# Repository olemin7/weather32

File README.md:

weather stantion
redused CPU frequency to 80
# Troubleshooting

* Program upload failure

    * Hardware connection is not correct: run `idf.py -p PORT monitor`, and reboot your board to see if there are any output logs.
    * The baud rate for downloading is too high: lower your baud rate in the `menuconfig` menu, and try again.

https://esp-idf-lib.readthedocs.io/en/latest/groups/bmp180.html

https://github.com/espressif/esp-iot-solution

# esp32c3_supermini
    Pin     | ADC | func |
GPIO_NUM_0  | A0  |      |photoresistor
GPIO_NUM_1  | A1  |      |service switch
GPIO_NUM_2  | A2  |      |
GPIO_NUM_3  | A3  |      |
GPIO_NUM_4  | A4  | SCK  | 
3V3
GND
5V
-------------------------------------
GPIO_NUM_5  | A5  | MISO |
GPIO_NUM_6  |     | MOSI | bme680 SDA !!! swap in new PCB version
GPIO_NUM_7  |     | SS   | bme680 SDL
GPIO_NUM_8  |     | SDA  | LED           
GPIO_NUM_9  |     | SDL  | BOOT_BUTTON   
GPIO_NUM_10 |     |      |
GPIO_NUM_20 |     | RX   |
GPIO_NUM_21 |     | TX   |

https://github.com/DiegoPaezA/ESP32-freeRTOS/blob/master/i2c_scanner/main/i2c_scanner.c
https://github.com/espressif/esp-iot-solution/tree/dd15770d0f8c5fedea78809737f04b63d3765c83/examples/sensors/sensor_hub_monitor

. /home/oleksandr/ides/tools/esp-idf-v5.3/export.sh
export IOT_SOLUTION_PATH=/home/oleksandr/personal/repo/esp-iot-solution
idf.py set-target esp32c3
idf.py build
idf.py menuconfig

null in the env https://github.com/espressif/idf-eclipse-plugin/issues/535https://components.espressif.com/

Check the values in your sdkconfig for LOG_MAXIMUM_LEVEL. It defaults to matching LOG_DEFAULT_LEVEL which limits what values you can use by default.

# mqtt test
sudo apt-get install mosquitto mosquitto-clients

sudo vim /etc/mosquitto/mosquitto.conf 
add
  listener 1883 0.0.0.0
  allow_anonymous true

sudo ufw allow 1883

sudo /etc/init.d/mosquitto restart

mosquitto_sub -h nas.local -d -t advertisement
mosquitto_pub -h nas.local -d -t cmd -m "adv"
mosquitto_sub -h 192.168.1.2 -d -t devices/64E833880880/#

one terminal
mosquitto_sub -d -t hello/world
mosquitto_sub -d -t stat/weather -h central.local
Connect to another ssh session and run
mosquitto_pub -d -t hello/world -m "Hello from terminal window 2!"

sudo tail -f /var/log/mosquitto/mosquitto.log

mosquitto_sub -h nas.local -d -t '#'
https://github.com/nopnop2002/esp-idf-json/tree/master/json-basic-object

# button
todo boot btn to go provision mode?

# esp-idf-lib
https://esp-idf-lib.readthedocs.io/en/latest/index.html
git clone git@github.com:UncleRus/esp-idf-lib.git

# dependency
https://github.com/olemin7/esp32_idf_libs

# TP4056  li ion charger
max 4.2
min 2.5
## li ion
max 4.2
min 3.0

## attenuation
ADC_ATTEN_DB_0   100 mV ~ 950 mV
ADC_ATTEN_DB_2_5 100 mV ~ 1250 mV
ADC_ATTEN_DB_6   150 mV ~ 1750 mV
ADC_ATTEN_DB_12  150 mV ~ 2450 mV

https://docs.espressif.com/projects/esp-idf/en/v4.4.8/esp32/api-reference/peripherals/adc.html
#photoresistor (GND ) -photoresistor- (A0) -resistor 10k- (+3.3)

# LiIon
min 
https://esp32tutorials.com/esp32-esp-idf-max7219-dot-matrix-display

[json]
https://github.com/nopnop2002/esp-idf-json

# cmd list
export TARGET_MAC=64E833885558
export TARGET_MAC=64E833880880
export TARGET_MAC=64E83387D7D0
export TARGET_MAC=64E8338811DC
mosquitto_sub -d -t response/$TARGET_MAC -h nas.local
mosquitto_sub -d -t devices/$TARGET_MAC/# -h nas.local

mosquitto_pub -d -t cmd/$TARGET_MAC -m '{"cmd":"help"}' -h nas.local

mosquitto_pub -d -t cmd/$TARGET_MAC -m '{"cmd":"ldr","payload":{"min":100,"max":3000}}' -h nas.local
mosquitto_pub -d -t cmd/$TARGET_MAC -m '{"cmd":"restart"}' -h nas.local

mosquitto_pub -d -t cmd/$TARGET_MAC -m '{"cmd":"brightness","payload":{"points":[{"lighting":1530,"brightness":10}]}}' -h nas.local

mosquitto_pub -d -t cmd/$TARGET_MAC -m -h nas.local '{"cmd":"brightness","payload":{"points":[{"lighting":1530,"brightness":10}]}}' 

{"cmd":"display","payload":{"segment_rotation":0,"segment_upsidedown":false,"mirrored":false}}

'{"cmd":"display","payload":{"segment_rotation":3,"segment_upsidedown":true,"mirrored":true}}

'{"cmd":"timezone","payload":{"tz":"GMT-3"}}'

[http command server]
url /cmd
smd the same as for mosqitoo
[IDF_PATH]

printenv IDF_PATH

export IDF_PATH="/home/oleksandrminenko/personal/esp-idf/v5.4/esp-idf"

[TODO]
custom data when provision

[test]
https://www.throwtheswitch.org/unity
idf.py -p /dev/ttyACM0 flash

[mink]
long press on boot btn ->reprovision

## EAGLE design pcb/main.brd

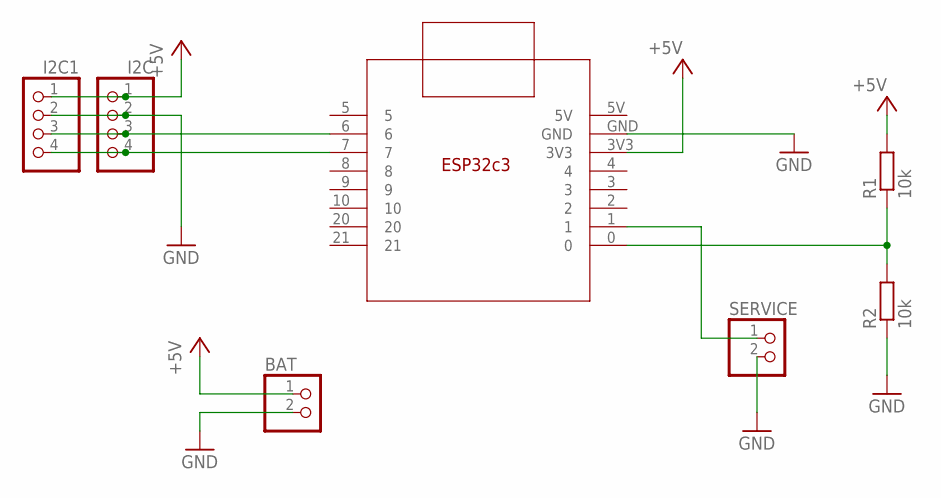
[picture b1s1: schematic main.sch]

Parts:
BAT: PINHD-1X2; 1X02
I2C, I2C1: PINHD-1X4; 1X04
R1, R2: 10k; R0805
SERVICE: PINHD-1X2; 1X02
U$2: ESP32C3SMD; ESP32C3_SMD

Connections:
+5V: BAT.1, I2C.1, I2C1.1, R1.2, U$2.3V3
GND: BAT.2, I2C.2, I2C1.2, R2.1, SERVICE.2, U$2.GND
unnamed: I2C.3, I2C1.3, U$2.6
unnamed: R1.1, R2.2, U$2.0
unnamed: I2C.4, I2C1.4, U$2.7
unnamed: SERVICE.1, U$2.1

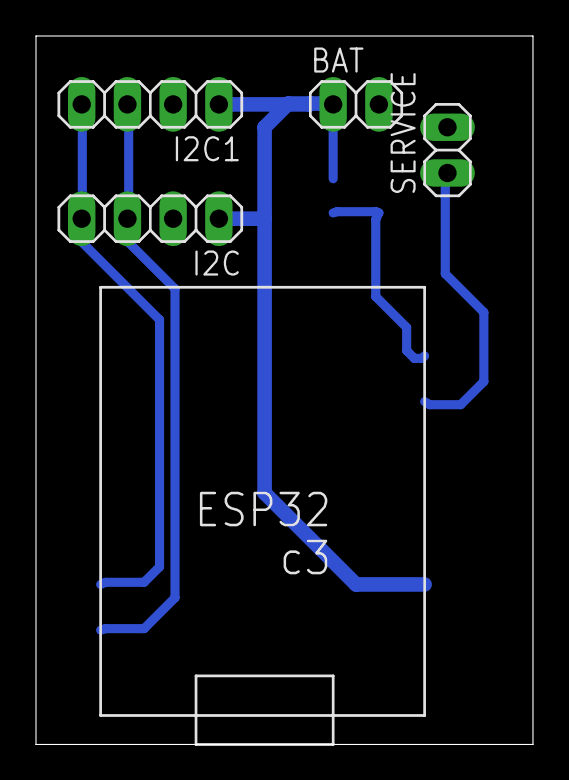
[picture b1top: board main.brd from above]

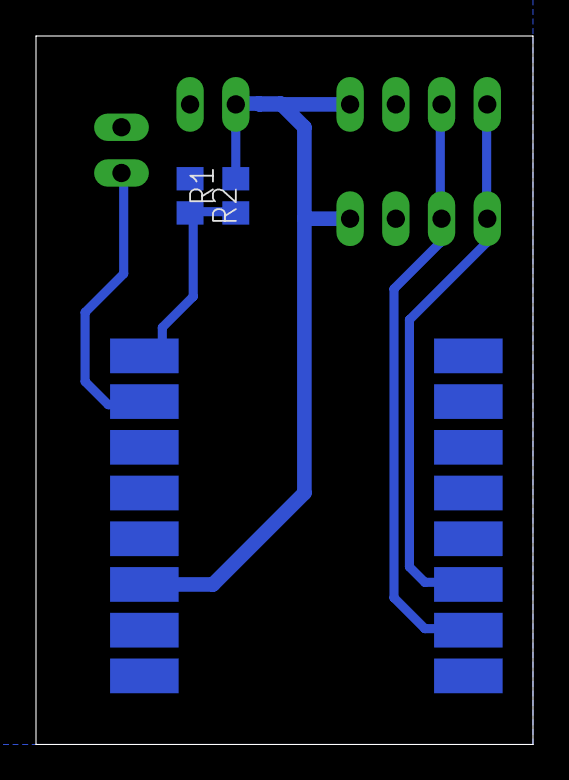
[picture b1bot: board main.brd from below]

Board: 2 copper layers, 27.6 x 39.4 mm, 7 parts (2 on the bottom side), 6 nets.

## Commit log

2024-06-15 initial
2024-07-01 build
2024-07-01 blink
2024-08-25 bme280
2024-08-27 mqtt
2024-08-28 sleep
2024-08-30 refact
2025-09-18 initial 2
2025-09-27 init
2025-10-05 bme680
2025-10-06 add void cmd handler
2025-10-07 add bh1750
2025-10-08 optimise deepsleep
2025-10-09 posising sensors
2025-10-09 adc initial
2025-10-10 switch
2025-10-17 err handling
2025-10-20 change i2c line
2025-10-25 update sensors boot handling
2025-11-25 sleep duartion
2025-11-25 move common files to the libraries
2025-11-27 synk to libs
2026-02-03 use managed library
2026-02-03 improve build
